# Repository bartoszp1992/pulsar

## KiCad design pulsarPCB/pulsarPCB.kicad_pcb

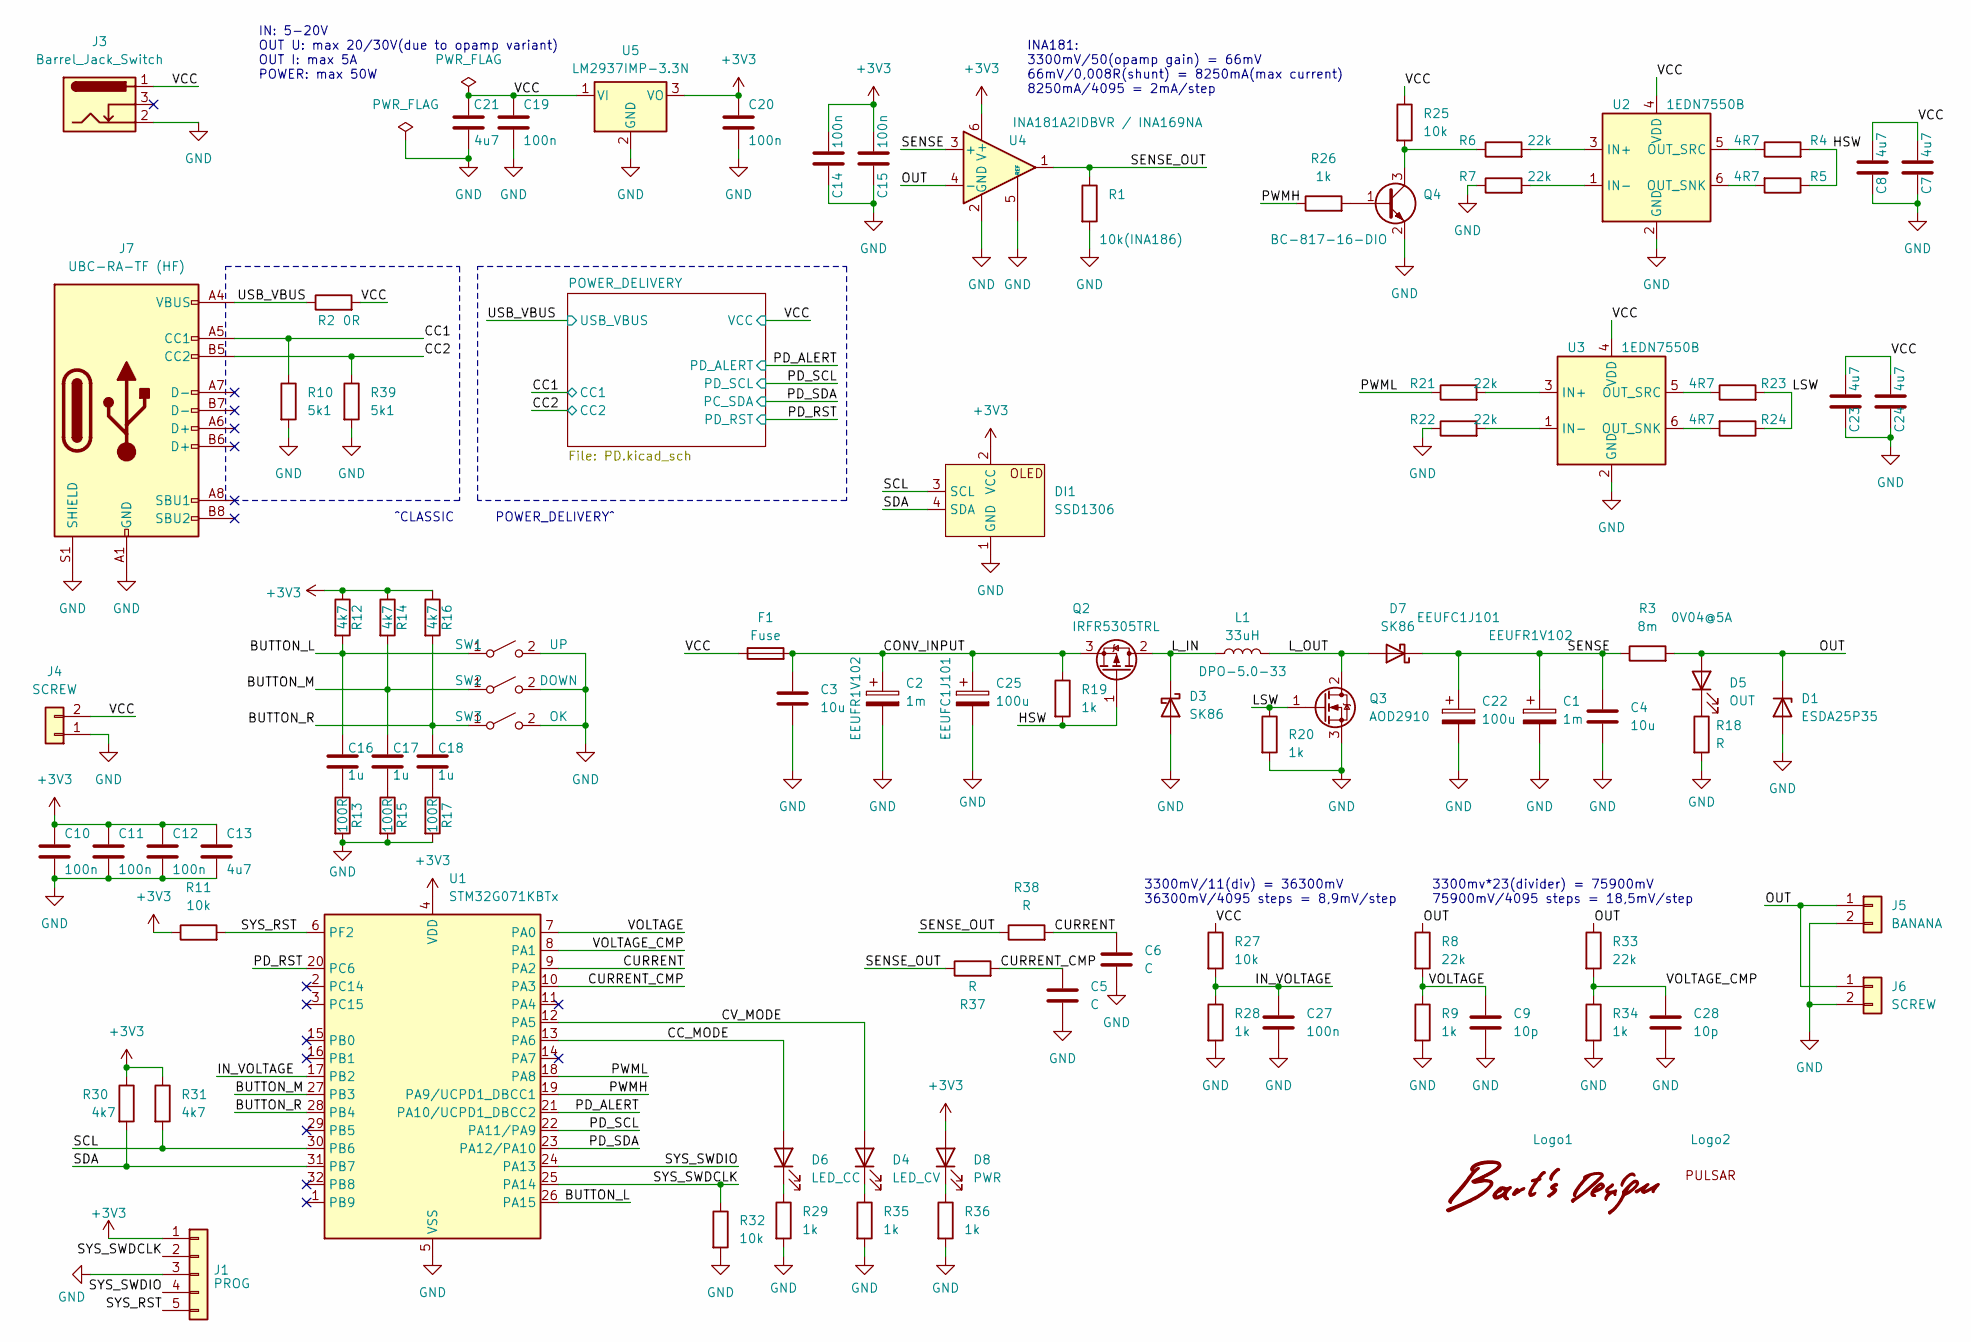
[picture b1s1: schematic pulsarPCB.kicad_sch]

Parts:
C1, C2: 1m; CP_Radial_D12.5mm_P5.00mm
C3, C4: 10u; C_1206_3216Metric
C5, C6: C; C_0603_1608Metric
C7, C8, C13, C21, C23, C24: 4u7; C_1206_3216Metric
C9, C28: 10p; C_0603_1608Metric
C10, C11, C12, C14, C15, C19, C20, C27: 100n; C_0603_1608Metric
C16, C17, C18: 1u; C_0603_1608Metric
C22, C25: 100u; CP_Radial_D10.0mm_P5.00mm
D1: ESDA25P35; D_0603_1608Metric
D3, D7: SK86; D_SMC
D4: LED_CV; LED_0603_1608Metric
D5: OUT; LED_0603_1608Metric
D6: LED_CC; LED_0603_1608Metric
D8: PWR; LED_0603_1608Metric
DI1: SSD1306
F1: Fuse; Fuse_1206_3216Metric
J1: PROG; PinHeader_1x05_P2.54mm_Vertical
J3: Barrel_Jack_Switch; BarrelJack_Horizontal
J4, J6: SCREW; DEGSON DG301-5.0-2.0P
J5: BANANA; BANANA 4mm
J7: UBC-RA-TF (HF)
L1: 33uH; DPO-5.0-33
Logo1: Bart's Design
Logo2: PULSAR
Q2: IRFR5305TRL; TO-252-2
Q3: AOD2910; TO-252-2
Q4: BC-817-16-DIO; SOT-23
R1: 10k(INA186); R_0603_1608Metric
R2: 0R; D_0603_1608Metric
R3: 8m; R_2512_6332Metric
R4, R5, R23, R24: 4R7; R_1206_3216Metric
R6, R7, R8, R21, R22, R33: 22k; R_0603_1608Metric
R9, R19, R20, R26, R28, R29, R34, R35, R36: 1k; R_0603_1608Metric
R10, R39: 5k1; R_0603_1608Metric
R11, R25, R27, R32: 10k; R_0603_1608Metric
R12, R14, R16, R30, R31: 4k7; R_0603_1608Metric
R13, R15, R17: 100R; R_0805_2012Metric
R18, R37, R38: R; R_0603_1608Metric
SW1: UP; SW_PUSH_6mm
SW2: DOWN; SW_PUSH_6mm
SW3: OK; SW_PUSH_6mm
U1: STM32G071KBTx; LQFP-32_7x7mm_P0.8mm
U2, U3: 1EDN7550B; SOT-23-6
U4: INA181A2IDBVR / INA169NA; SOT-23-6
U5: LM2937IMP-3.3N; SOT-223-3_TabPin2

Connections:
+3V3: C10.1, C11.1, C12.1, C13.1, C14.2, C15.2, C20.1, D8.2 (A), DI1.2 (VCC), J1.1, R11.1, R12.1, R14.1, R16.1, R30.1, R31.1, U1.4 (VDD), U4.6 (V+), U5.3 (VO); also elsewhere on the board
/BUTTON_L: C16.1, R12.2, SW1.1 (A), U1.26 (PA15)
/BUTTON_M: C17.1, R14.2, SW2.1 (A), U1.27 (PB3)
/BUTTON_R: C18.1, R16.2, SW3.1 (A), U1.28 (PB4)
/CC1: J7.A5 (CC1), R10.1; also elsewhere on the board
/CC2: J7.B5 (CC2), R39.1; also elsewhere on the board
/CC_MODE: D6.2 (A), U1.13 (PA6)
/CONV_INPUT: C2.1, C3.1, C25.1, F1.2, Q2.3 (S), R19.1
/CURRENT: C6.2, R38.2, U1.9 (PA2)
/CURRENT_CMP: C5.2, R37.2, U1.10 (PA3)
/CV_MODE: D4.2 (A), U1.12 (PA5)
/HSW: Q2.1 (G), R4.2, R5.1, R19.2
/IN_VOLTAGE: C27.1, R27.2, R28.1, U1.17 (PB2)
/LSW: Q3.1 (G), R20.1, R23.2, R24.1
/L_IN: D3.1 (K), L1.1, Q2.2 (D)
/L_OUT: D7.2 (A), L1.2, Q3.2 (D)
/OUT: D1.1 (K), D5.2 (A), J5.1, J6.1, R3.2, R8.1, R33.1, U4.4 (-)
/PD_ALERT: U1.21 (PA10/UCPD1_DBCC2); also elsewhere on the board
/PD_RST: U1.20 (PC6); also elsewhere on the board
/PD_SCL: U1.22 (PA11/PA9); also elsewhere on the board
/PD_SDA: U1.23 (PA12/PA10); also elsewhere on the board
/PWMH: R26.1, U1.19 (PA9/UCPD1_DBCC1)
/PWML: R21.1, U1.18 (PA8)
/SCL: DI1.3 (SCL), R31.2, U1.30 (PB6)
/SDA: DI1.4 (SDA), R30.2, U1.31 (PB7)
/SENSE: C1.1, C4.1, C22.1, D7.1 (K), R3.1, U4.3 (+)
/SENSE_OUT: R1.1, R37.1, R38.1, U4.1
/SYS_RST: J1.5, R11.2, U1.6 (PF2)
/SYS_SWDCLK: J1.2, R32.1, U1.25 (PA14)
/SYS_SWDIO: J1.4, U1.24 (PA13)
/USB_VBUS: J7.A4 (VBUS), J7.A9 (VBUS), J7.B4 (VBUS), J7.B9 (VBUS), R2.1; also elsewhere on the board
/VCC: C7.2, C8.2, C19.1, C21.2, C23.2, C24.2, F1.1, J3.1, J4.2, R2.2, R25.1, R27.1, U2.4 (VDD), U3.4 (VDD), U5.1 (VI); also elsewhere on the board
/VOLTAGE: C9.1, R8.2, R9.1, U1.7 (PA0)
/VOLTAGE_CMP: C28.1, R33.2, R34.1, U1.8 (PA1)
GND: C1.2, C2.2, C3.2, C4.2, C5.1, C6.1, C7.1, C8.1, C9.2, C10.2, C11.2, C12.2, C13.2, C14.1, C15.1, C19.2, C20.2, C21.1, C22.2, C23.1, C24.1, C25.2, C27.2, C28.2, D1.2 (A), D3.2 (A), DI1.1 (GND), J1.3, J3.2, J4.1, J5.2, J6.2, J7.A1 (GND), J7.A12 (GND), J7.B1 (GND), J7.B12 (GND), J7.S1 (SHIELD), Q3.3 (S), Q4.2 (E), R1.2, R7.1, R9.2, R10.2, R13.2, R15.2, R17.2, R18.2, R20.2, R22.1, R28.2, R29.2, R32.2, R34.2, R35.2, R36.2, R39.2, SW1.2 (B), SW2.2 (B), SW3.2 (B), U1.5 (VSS), U2.2 (GND), U3.2 (GND), U4.2 (GND), U4.5 (REF), U5.2 (GND); also elsewhere on the board
unnamed: C16.2, R13.1
unnamed: C17.2, R15.1
unnamed: C18.2, R17.1
unnamed: D4.1 (K), R35.1
unnamed: D5.1 (K), R18.1
unnamed: D6.1 (K), R29.1
unnamed: D8.1 (K), R36.1
unnamed: Q4.1 (B), R26.2
unnamed: Q4.3 (C), R6.1, R25.2
unnamed: R6.2, U2.3 (IN+)
unnamed: R7.2, U2.1 (IN-)
unnamed: R5.2, U2.6 (OUT_SNK)
unnamed: R4.1, U2.5 (OUT_SRC)
unnamed: R21.2, U3.3 (IN+)
unnamed: R22.2, U3.1 (IN-)
unnamed: R24.2, U3.6 (OUT_SNK)
unnamed: R23.1, U3.5 (OUT_SRC)

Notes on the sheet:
IN: 5-20V OUT U: max 20/30V(due to opamp variant) OUT I: max 5A POWER: max 50W
3300mV/11(div) = 36300mV 36300mV/4095 steps = 8,9mV/step
3300mv*23(divider) = 75900mV 75900mV/4095 steps = 18,5mV/step
^CLASSIC POWER_DELIVERY^
INA181: 3300mV/50(opamp gain) = 66mV 66mV/0,008R(shunt) = 8250mA(max current) 8250mA/4095 = 2mA/step

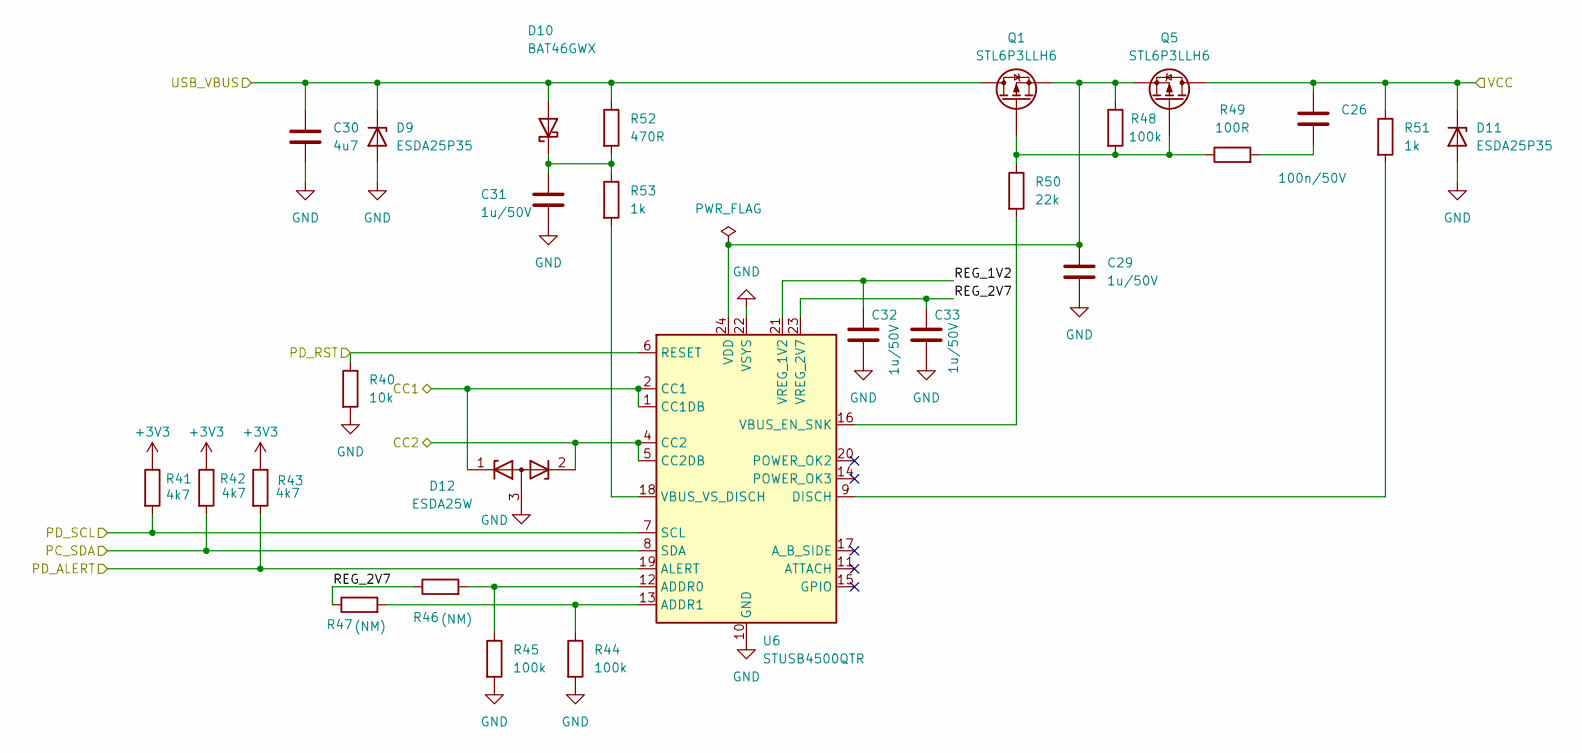
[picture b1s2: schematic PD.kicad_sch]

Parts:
C26: 100n/50V; C_0603_1608Metric
C29, C31, C32, C33: 1u/50V; C_0603_1608Metric
C30: 4u7; C_1206_3216Metric
D9, D11: ESDA25P35; D_0603_1608Metric
D10: BAT46GWX; D_SOD-123
D12: ESDA25W; SOT-323L
Q1, Q5: STL6P3LLH6; PowerFLAT 3.3x3.3
R40: 10k; R_0603_1608Metric
R41, R42, R43: 4k7; R_0603_1608Metric
R44, R45, R48: 100k; R_0603_1608Metric
R46, R47: (NM); R_0603_1608Metric
R49: 100R; R_0805_2012Metric
R50: 22k; R_0603_1608Metric
R51, R53: 1k; R_0603_1608Metric
R52: 470R; R_0603_1608Metric
U6: STUSB4500QTR; QFN-24-1EP_4x4mm_P0.5mm_EP2.7x2.7mm

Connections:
+3V3: R41.1, R42.1, R43.1; also elsewhere on the board
/CC1: D12.1 (K), U6.1 (CC1DB), U6.2 (CC1); also elsewhere on the board
/CC2: D12.2 (K), U6.4 (CC2), U6.5 (CC2DB); also elsewhere on the board
/PD_ALERT: R43.2, U6.19 (ALERT); also elsewhere on the board
/PD_RST: R40.1, U6.6 (RESET); also elsewhere on the board
/PD_SCL: R41.2, U6.7 (SCL); also elsewhere on the board
/PD_SDA: R42.2, U6.8 (SDA); also elsewhere on the board
/POWER_DELIVERY/REG_1V2: C32.1, U6.21 (VREG_1V2)
/POWER_DELIVERY/REG_2V7: C33.1, R46.1, R47.1, U6.23 (VREG_2V7)
/USB_VBUS: C30.1, D9.1 (K), D10.2 (A), Q1.5 (D), Q1.6 (D), Q1.7 (D), Q1.8 (D), R52.1; also elsewhere on the board
/VCC: C26.1, D11.1 (K), Q5.5 (D), Q5.6 (D), Q5.7 (D), Q5.8 (D), R51.1; also elsewhere on the board
GND: C29.2, C30.2, C31.2, C32.2, C33.2, D9.2 (A), D11.2 (A), D12.3 (A), R40.2, R44.2, R45.2, U6.10 (GND), U6.22 (VSYS), U6.25 (GND); also elsewhere on the board
unnamed: C26.2, R49.2
unnamed: C31.1, D10.1 (K), R52.2, R53.1
unnamed: Q1.4 (G), Q5.4 (G), R48.2, R49.1, R50.1
unnamed: R45.1, R46.2, U6.12 (ADDR0)
unnamed: R44.1, R47.2, U6.13 (ADDR1)
unnamed: R51.2, U6.9 (DISCH)
unnamed: R50.2, U6.16 (VBUS_EN_SNK)
unnamed: R53.2, U6.18 (VBUS_VS_DISCH)
unnamed: C29.1, Q1.1 (S), Q1.2 (S), Q1.3 (S), Q5.1 (S), Q5.2 (S), Q5.3 (S), R48.1, U6.24 (VDD)

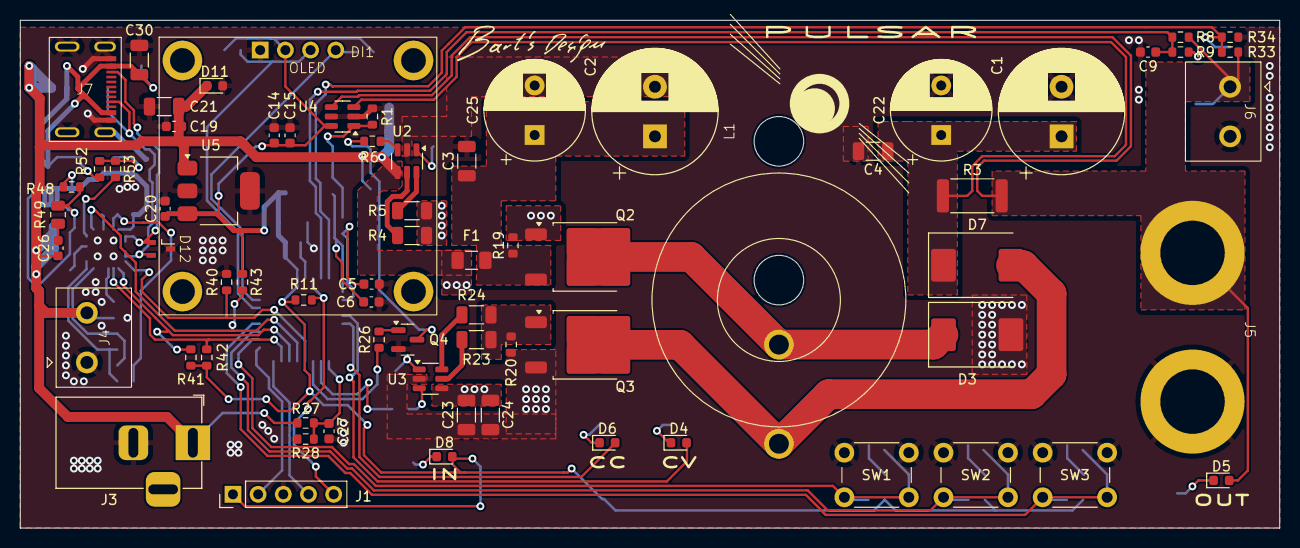
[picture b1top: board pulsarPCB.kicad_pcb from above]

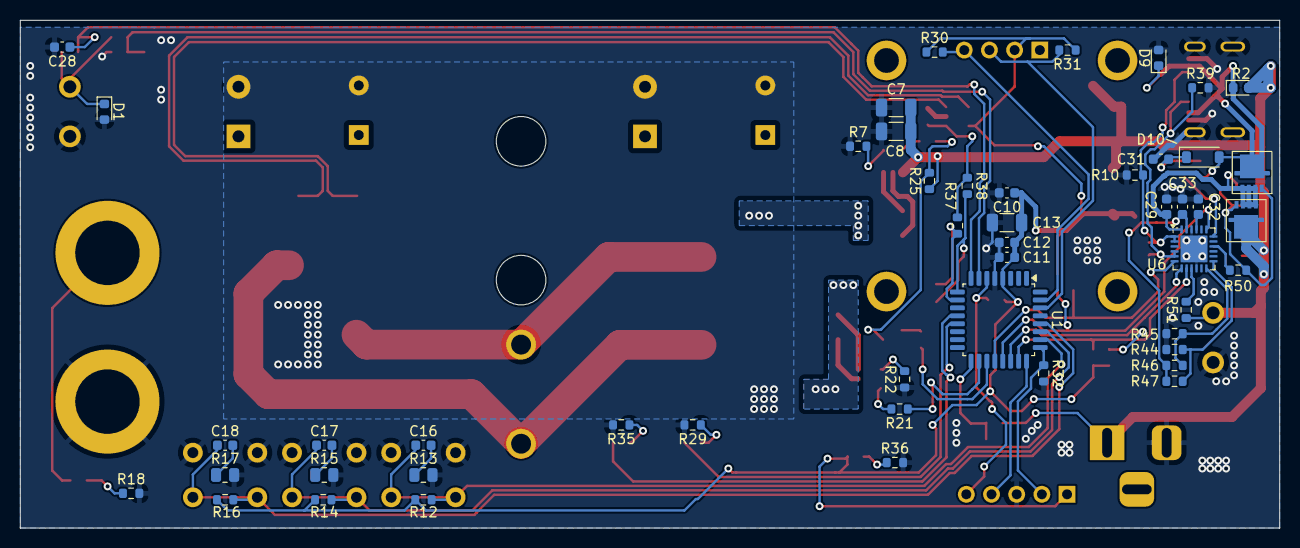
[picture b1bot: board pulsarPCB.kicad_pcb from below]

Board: 2 copper layers, 127.0 x 51.2 mm, 122 parts (49 on the bottom side), 63 nets.

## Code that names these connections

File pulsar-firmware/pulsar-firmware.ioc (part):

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Mcu.Name=STM32G071K(6-8-B)Tx
Mcu.Package=LQFP32
Mcu.UserName=STM32G071KBTx
PA0.GPIOParameters=GPIO_Label
PA0.GPIO_Label=VOLTAGE
PA0.Mode=IN0
PA0.Signal=ADC1_IN0
PA1.GPIOParameters=GPIO_Label
PA1.GPIO_Label=VOLTAGE_CMP
PA1.Mode=INP
PA1.Signal=COMP1_INP
PA10.GPIOParameters=GPIO_Label
PA10.GPIO_Label=PD_ALERT
PA10.Signal=GPIO_Input
PA11\ [PA9].Mode=I2C
PA11\ [PA9].Signal=I2C2_SCL
PA12\ [PA10].Mode=I2C
PA12\ [PA10].Signal=I2C2_SDA
PA13.Mode=Serial_Wire
PA13.Signal=SYS_SWDIO
PA14-BOOT0.Mode=Serial_Wire
PA14-BOOT0.Signal=SYS_SWCLK
PA15.GPIOParameters=GPIO_Label
PA15.GPIO_Label=BUTTON_RIGHT
PA15.Signal=GPIO_Input
PA2.GPIOParameters=GPIO_Label
PA2.GPIO_Label=CURRENT
PA2.Mode=IN2
PA2.Signal=ADC1_IN2
PA3.GPIOParameters=GPIO_Label
PA3.GPIO_Label=CURRENT_COMP
PA3.Mode=INP
PA3.Signal=COMP2_INP
PA5.GPIOParameters=GPIO_Label
PA5.GPIO_Label=LED_CV
PA5.Signal=GPIO_Output
PA6.GPIOParameters=GPIO_Label
PA6.GPIO_Label=LED_CC
PA6.Signal=GPIO_Output
PA8.GPIOParameters=GPIO_Label
PA8.GPIO_Label=LOW_SW_CH1
PA8.Signal=S_TIM1_CH1
PA9.GPIOParameters=GPIO_Label
PA9.GPIO_Label=HIGH_SW_CH2
PA9.Signal=S_TIM1_CH2
PB2.GPIOParameters=GPIO_Label
PB2.GPIO_Label=INPUT_VOLTAGE
PB2.Mode=IN10
PB2.Signal=ADC1_IN10
PB3.GPIOParameters=GPIO_Label
PB3.GPIO_Label=BUTTON_MID
PB3.Signal=GPIO_Input
PB4.GPIOParameters=GPIO_Label
PB4.GPIO_Label=BUTTON_LEFT
PB4.Signal=GPIO_Input
PB6.GPIOParameters=GPIO_Pu
PB6.GPIO_Pu=GPIO_PULLUP
PB6.Mode=I2C
PB6.Signal=I2C1_SCL
PB7.GPIOParameters=GPIO_Pu
PB7.GPIO_Pu=GPIO_PULLUP
PB7.Mode=I2C
PB7.Signal=I2C1_SDA
PC6.GPIOParameters=GPIO_Label
PC6.GPIO_Label=PD_RST
PC6.Signal=GPIO_Output
RCC.HSE_VALUE=8000000
RCC.SYSCLKFreq_VALUE=64000000
RCC.SYSCLKSource=RCC_SYSCLKSOURCE_PLLCLK
board=custom

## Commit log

2024-02-06 initial
2024-02-08 change topology
2024-03-15 PCB v1
